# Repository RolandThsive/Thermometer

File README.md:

<div align="center">

# The Thermometer
### *An analog temperature & dew point gauge — part of the AQI Board*

</div>

---

## Overview

This repository is a part of the **AQI Board** project by [@RolandThsive](https://ro-h-bots.blogspot.com/p/about-me.html) — a wall of analog-style instruments (hygrometer, thermometer, AQI meter and VOC meter) that are as much a showpiece as they are useful.

The Thermometer shows **room temperature** and **dew point** with two independent mechanical ticks, each driven by its own N20 motor and tracked by its own absolute encoder.

| Tick | Shows | Drive train |
| :--- | :--- | :--- |
| **Tick 1** — brass rod | Room temperature | N20 → crossed helical gear → two 22T spur gears → tick |
| **Tick 2** — planetary set | Dew point | N20 → crossed helical gear → helical ring gear → planetary set |

Both ticks are read **1 : 1** by AS5600 magnetic encoders on the main board, so the gauge always knows exactly where its needles are. Gear visibility and a symmetrical face were the top design priorities.

---

## Features

- **Absolute positioning** on both ticks with AS5600 magnetic encoders
- **Planetary gear set** as the visual centrepiece of the face
- **Custom main board** built around a Seeed Studio XIAO ESP32-C3
- **PCA9546A I²C multiplexer** to talk to both encoders and the SHT40 sensor
- **DRV8833** dual motor driver, with reverse-polarity and ESD protection on the connectors
- **USART link** (115200 baud) so the gauge can be polled and commanded by a master board
- **125 mm glass** front and a two-part 3D-printed housing with embedded nuts

---

## Parts Gallery

<div align="center">

| Full Assembly | Both Ticks Engaged | Main Board |
| :---: | :---: | :---: |
|  |  |  |
| **Top Assembly** | **Bottom Assembly** | **Top Housing** |
|  |  |  |

*Want to spin these around? The blog post has interactive 3D viewers for every assembly.*

</div>

---

## Instructions

For complete printing and assembly instructions, scroll all the way down to the **'Manufacturing'** section on the official blog post:
[The Thermometer (AQI Board) Guide](https://ro-h-bots.blogspot.com/2026/07/the-thermometer-aqi-board.html)

> [!TIP]
> Every part prints normally **except the top housing**, which has nuts embedded mid-print. The layer they sit on must be perfectly flat — use the [Sharpie technique](https://www.youtube.com/shorts/kZ-3rjznSyk) on the supports.

---

## Bill of Materials (BOM)

| Quantity | Item Description |
| :---: | :--- |
| **8x** | M2 x 16 mm Hex Head Allen Type Screws |
| **8x** | M2 Nut |
| **2x** | N20 motor |
| **1x** | Set of 3D printed parts *(Found in the `CAD/Printables` folder)* |
| **1x** | Fully Assembled Circuit *(Found in the `Electronics` folder)*|
| **1x** | 2mm Brass rod *(Cut to size)* |
| **6x** | 15mm x 5mm N52 Neodymium magnets |
| **1x** | 120mm x 120mm PC fan |
| **1x** | 0.6mm PVC mesh *(Cut to size)* |
| **1x** | 1 set of 5-pin pogo pin connector |
| **1x** | SKF 688 Bearing |
| **2x** | NMB MR74 Bearing |
| **2x** | NMB MR63 Bearing |
| **1x** | NMB MR126 Bearing |
| **4x** | SKF 696 Bearing |

---

## Electronics

| Component | Role |
| :--- | :--- |
| Seeed Studio XIAO ESP32-C3 | Main controller |
| SHT40 | Temperature & humidity sensor (dew point is calculated from these) |
| AS5600 ×2 | Absolute magnetic encoders, one per tick |
| PCA9546A | 4-channel I²C multiplexer |
| DRV8833 | Dual H-bridge motor driver |
| DMP3007LK3 | P-MOSFET for reverse-polarity protection |
| USBLC6-2 | ESD protection |

Schematic PDF: [`Electronics/TheMainBoard_Schematic.pdf`](Electronics/TheMainBoard_Schematic.pdf) · KiCad project, custom symbol/footprint libraries, Gerbers and datasheets are all in [`Electronics/`](Electronics).

---

## Firmware

Built with **PlatformIO** on the Arduino framework for `seeed_xiao_esp32c3`.

```bash
cd Firmware/temperature_level_device
pio run -t upload
pio device monitor -b 115200
```

| Command (over USART) | Response |
| :---: | :--- |
| `t` | Reads the SHT40 and returns temperature and dew point as binary floats |
| `w` | Moves the ticks to the latest temperature and dew point |

Between commands the gauge refreshes itself on its own, so it also works standalone.

`Firmware/Testing Programs/` holds the bring-up sketches used along the way: motor silence tests (plain and PID), USART master communication, and a PCA9546A device scanner.

---

## Repository Structure

```
Thermometer/
├── CAD/
│   ├── Blender Projects/        # Source .blend files for every assembly
│   ├── GLB-GLTF FIles/          # Web-ready 3D models + model-viewer pages
│   ├── Printables/              # STL files to print
│   └── Step Files/              # STEP assemblies (with and without electronics)
├── Electronics/
│   ├── The Main Board/          # KiCad project + Gerber files
│   ├── Libraries/               # Custom KiCad symbols, footprints & 3D models
│   ├── Documentations/          # Component datasheets
│   └── TheMainBoard_Schematic.pdf
├── Firmware/
│   ├── temperature_level_device/     # Main firmware
│   ├── temperature_level_device_2/   # Alternate firmware revision
│   └── Testing Programs/             # Bring-up & test sketches
├── LICENSE.txt
└── README.md
```

---

## The AQI Board Family

| Project | Description |
| :--- | :--- |
| [**Hygrometer**](https://github.com/RolandThsive/Hygrometer) | Analog humidity gauge with a globoid worm drive |
| **Thermometer** *(you are here)* | Temperature & dew point gauge with a planetary gear set |
| AQI Meter · VOC Meter | Coming soon |

---

## Gallery

<div align="center">

| Full Assembly | The Face |
| :---: | :---: |
|  |  |

| The Mechanism | The Main PCB — Assembled | The Backside |
| :---: | :---: | :---: |
|  |  |  |

| The Internals | The Main PCB — Front & Back |
| :---: | :---: |
|  |  |

**The Main Board Schematic**

*Click any picture to see it full size.*

</div>

---

## Connect With Me
* **Blog:** [ro-h-bots.blogspot.com](https://ro-h-bots.blogspot.com/)
* **Insta:** [@ro_h_bots](https://www.instagram.com/ro_h_bots?igsh=cDNkcnNpYnB5aWR1)

---

## License

[![CC BY-NC-SA 4.0][cc-by-nc-sa-shield]][cc-by-nc-sa]

This work is licensed under a [Creative Commons Attribution-NonCommercial-ShareAlike 4.0 International License][cc-by-nc-sa].

[![CC BY-NC-SA 4.0][cc-by-nc-sa-image]][cc-by-nc-sa]

[cc-by-nc-sa]: http://creativecommons.org/licenses/by-nc-sa/4.0/
[cc-by-nc-sa-image]: https://licensebuttons.net/l/by-nc-sa/4.0/88x31.png
[cc-by-nc-sa-shield]: https://img.shields.io/badge/License-CC%20BY--NC--SA%204.0-lightgrey.svg

<div align="center">

Made with love by **RolandThsive ([@RolandThsive](https://github.com/RolandThsive))**

</div>

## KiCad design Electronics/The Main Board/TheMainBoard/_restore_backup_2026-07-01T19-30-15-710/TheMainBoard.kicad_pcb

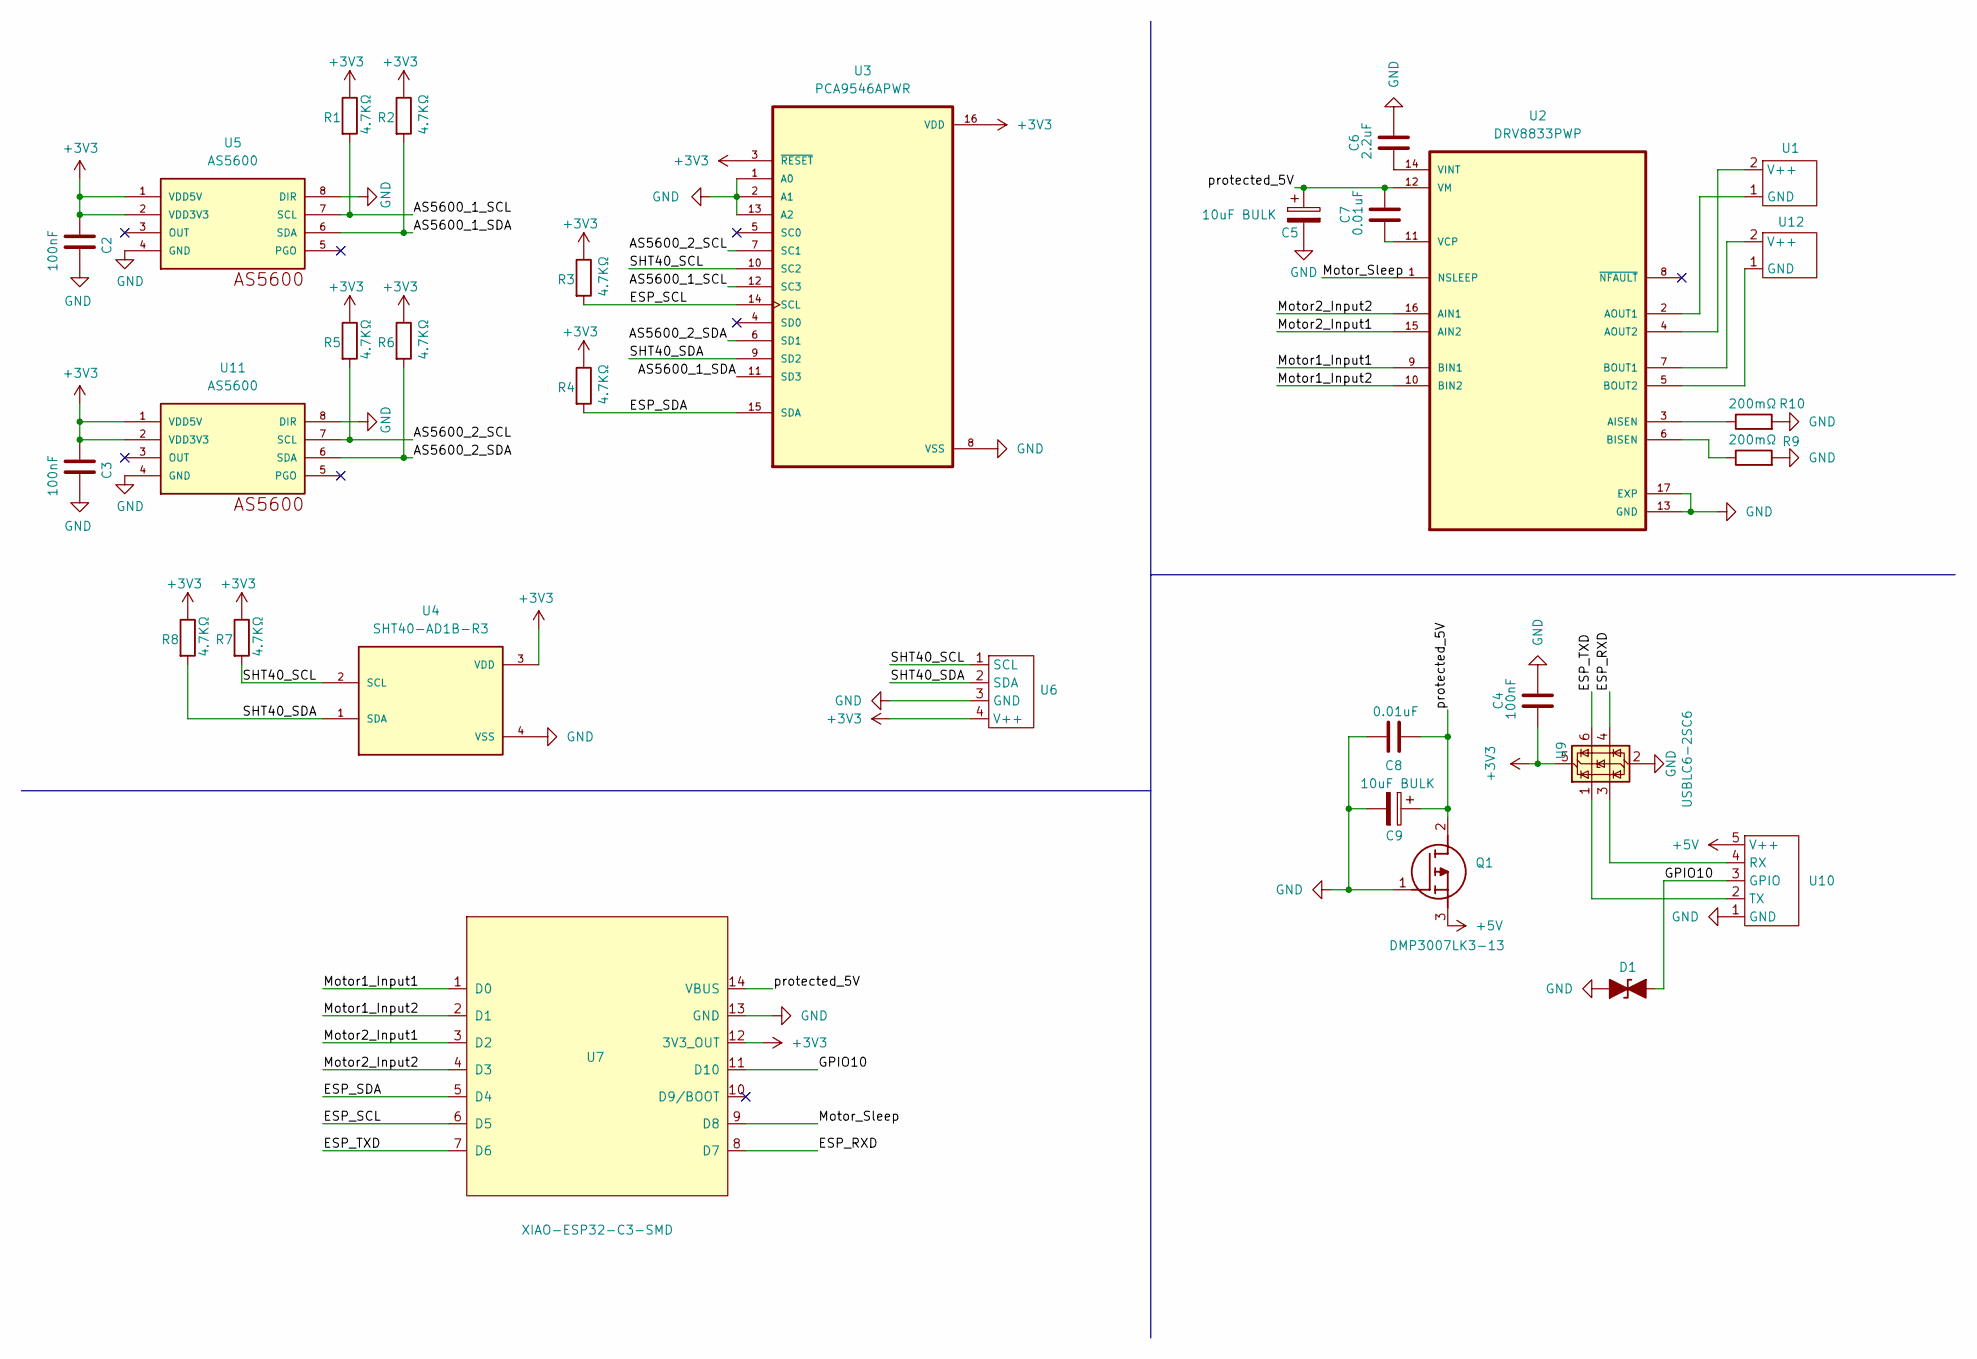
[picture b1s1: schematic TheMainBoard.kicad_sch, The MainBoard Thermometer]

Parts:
C2, C3, C4: 100nF; C_0805_2012Metric_Pad1.18x1.45mm_HandSolder
C5, C9: 10uF BULK; CP_EIA-3528-21_Kemet-B_HandSolder
C6: 2.2uF; C_0805_2012Metric_Pad1.18x1.45mm_HandSolder
C7, C8: 0.01uF; C_0805_2012Metric_Pad1.18x1.45mm_HandSolder
D1: D_TVS_Filled; R_0603_1608Metric_Pad0.98x0.95mm_HandSolder
Q1: DMP3007LK3-13; DMP3007LK313; Manufacturer_Part_Number DMP3007LK3-13; Mouser Part Number 621-DMP3007LK3-13
R1, R2, R3, R4, R5, R6, R7, R8: 4.7KΩ; R_0805_2012Metric_Pad1.20x1.40mm_HandSolder
R9, R10: 200mΩ; R_1206_3216Metric_Pad1.30x1.75mm_HandSolder
U1, U12: 2PinsOut_foot
U2: DRV8833PWP; IC_DRV8833PWP; PARTREV E
U3: PCA9546APWR; SOP65P640X120-16N
U4: SHT40-AD1B-R3; SHT4X
U5, U11: AS5600; SOIC8
U6: (no value)
U7: XIAO-ESP32-C3-SMD; XIAO-ESP32-C3-DIP
U9: USBLC6-2SC6; SOT-23-6
U10: 5PinsOut_foot

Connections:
+3V3: C2.1, C3.1, C4.1, R1.1, R2.1, R3.1, R4.1, R5.1, R6.1, R7.1, R8.1, U3.3 (~RESET), U3.16 (VDD), U4.3 (VDD), U5.1 (VDD5V), U5.2 (VDD3V3), U6.4 (V++), U7.12 (3V3_OUT), U9.5 (VBUS), U11.1 (VDD5V), U11.2 (VDD3V3)
+5V: Q1.3 (S), U10.5 (V++)
/AS5600_1_SCL: R1.2, U3.12 (SC3), U5.7 (SCL)
/AS5600_1_SDA: R2.2, U3.11 (SD3), U5.6 (SDA)
/AS5600_2_SCL: R5.2, U3.7 (SC1), U11.7 (SCL)
/AS5600_2_SDA: R6.2, U3.6 (SD1), U11.6 (SDA)
/ESP_RXD: U7.8 (D7), U9.4 (I/O2)
/ESP_SCL: R3.2, U3.14 (SCL), U7.6 (D5)
/ESP_SDA: R4.2, U3.15 (SDA), U7.5 (D4)
/ESP_TXD: U7.7 (D6), U9.6 (I/O1)
/GPIO10: D1.2 (A2), U7.11 (D10), U10.3 (GPIO)
/Motor1_Input1: U2.9 (BIN1), U7.1 (D0)
/Motor1_Input2: U2.10 (BIN2), U7.2 (D1)
/Motor2_Input1: U2.15 (AIN2), U7.3 (D2)
/Motor2_Input2: U2.16 (AIN1), U7.4 (D3)
/Motor_Sleep: U2.1 (NSLEEP), U7.9 (D8)
/SHT40_SCL: R7.2, U3.10 (SC2), U4.2 (SCL), U6.1 (SCL)
/SHT40_SDA: R8.2, U3.9 (SD2), U4.1 (SDA), U6.2 (SDA)
/protected_5V: C5.1, C7.2, C8.1, C9.1, Q1.2 (D), U2.12 (VM), U7.14 (VBUS)
GND: C2.2, C3.2, C4.2, C5.2, C6.2, C8.2, C9.2, D1.1 (A1), Q1.1 (G), R9.2, R10.2, U2.13 (GND), U2.17 (EXP), U3.1 (A0), U3.2 (A1), U3.8 (VSS), U3.13 (A2), U4.4 (VSS), U5.4 (GND), U5.8 (DIR), U6.3 (GND), U7.13 (GND), U9.2 (GND), U10.1 (GND), U11.4 (GND), U11.8 (DIR)
unnamed: U1.1 (GND), U2.2 (AOUT1)
unnamed: U1.2 (V++), U2.4 (AOUT2)
unnamed: R10.1, U2.3 (AISEN)
unnamed: R9.1, U2.6 (BISEN)
unnamed: C7.1, U2.11 (VCP)
unnamed: C6.1, U2.14 (VINT)
unnamed: U9.3 (I/O2), U10.4 (RX)
unnamed: U9.1 (I/O1), U10.2 (TX)
unnamed: U2.5 (BOUT2), U12.1 (GND)
unnamed: U2.7 (BOUT1), U12.2 (V++)

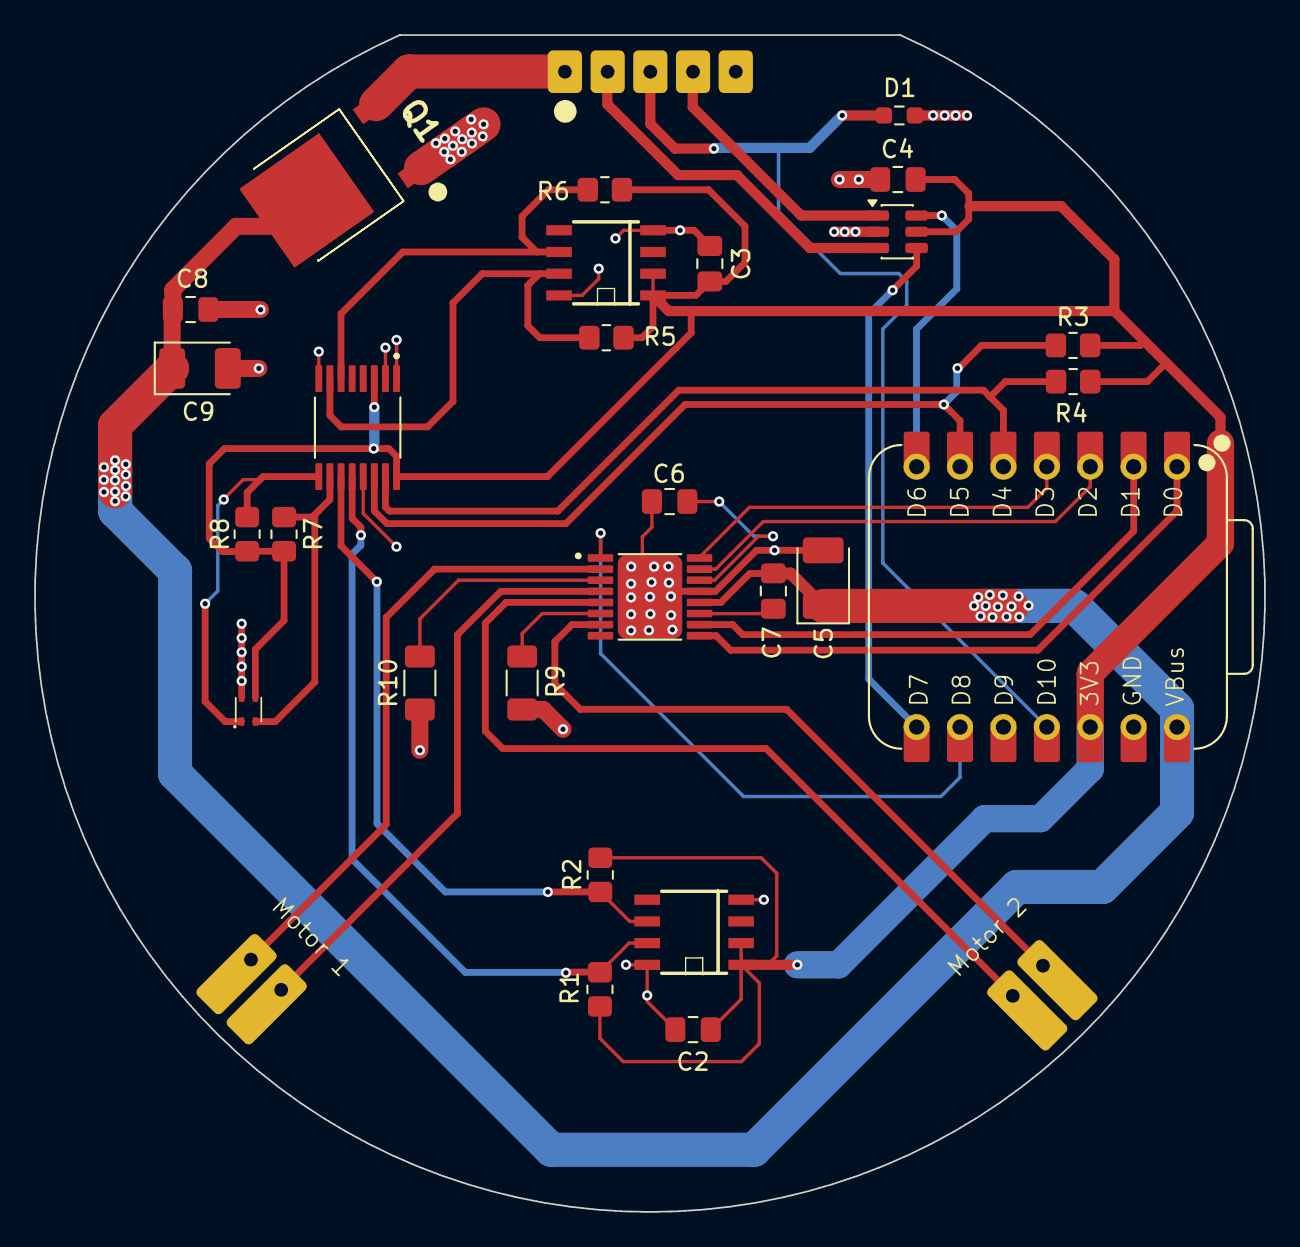
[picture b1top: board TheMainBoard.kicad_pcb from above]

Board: 2 copper layers, 72.0 x 68.9 mm, 30 parts (0 on the bottom side), 30 nets.
